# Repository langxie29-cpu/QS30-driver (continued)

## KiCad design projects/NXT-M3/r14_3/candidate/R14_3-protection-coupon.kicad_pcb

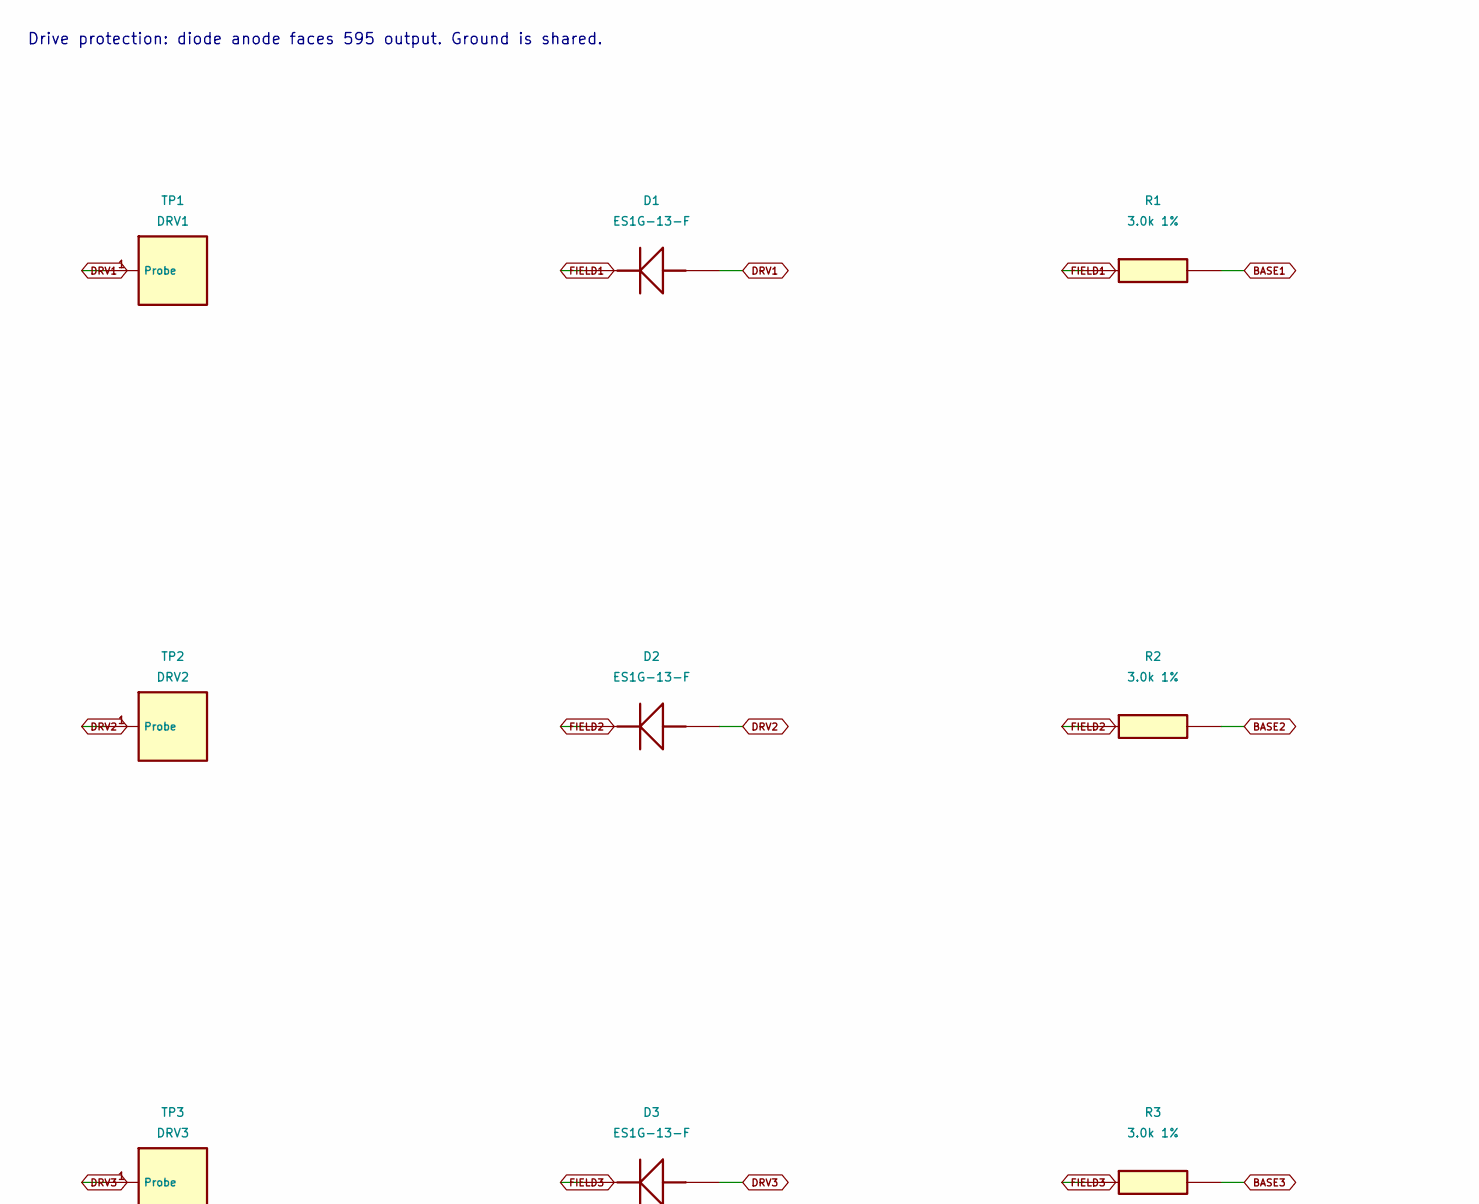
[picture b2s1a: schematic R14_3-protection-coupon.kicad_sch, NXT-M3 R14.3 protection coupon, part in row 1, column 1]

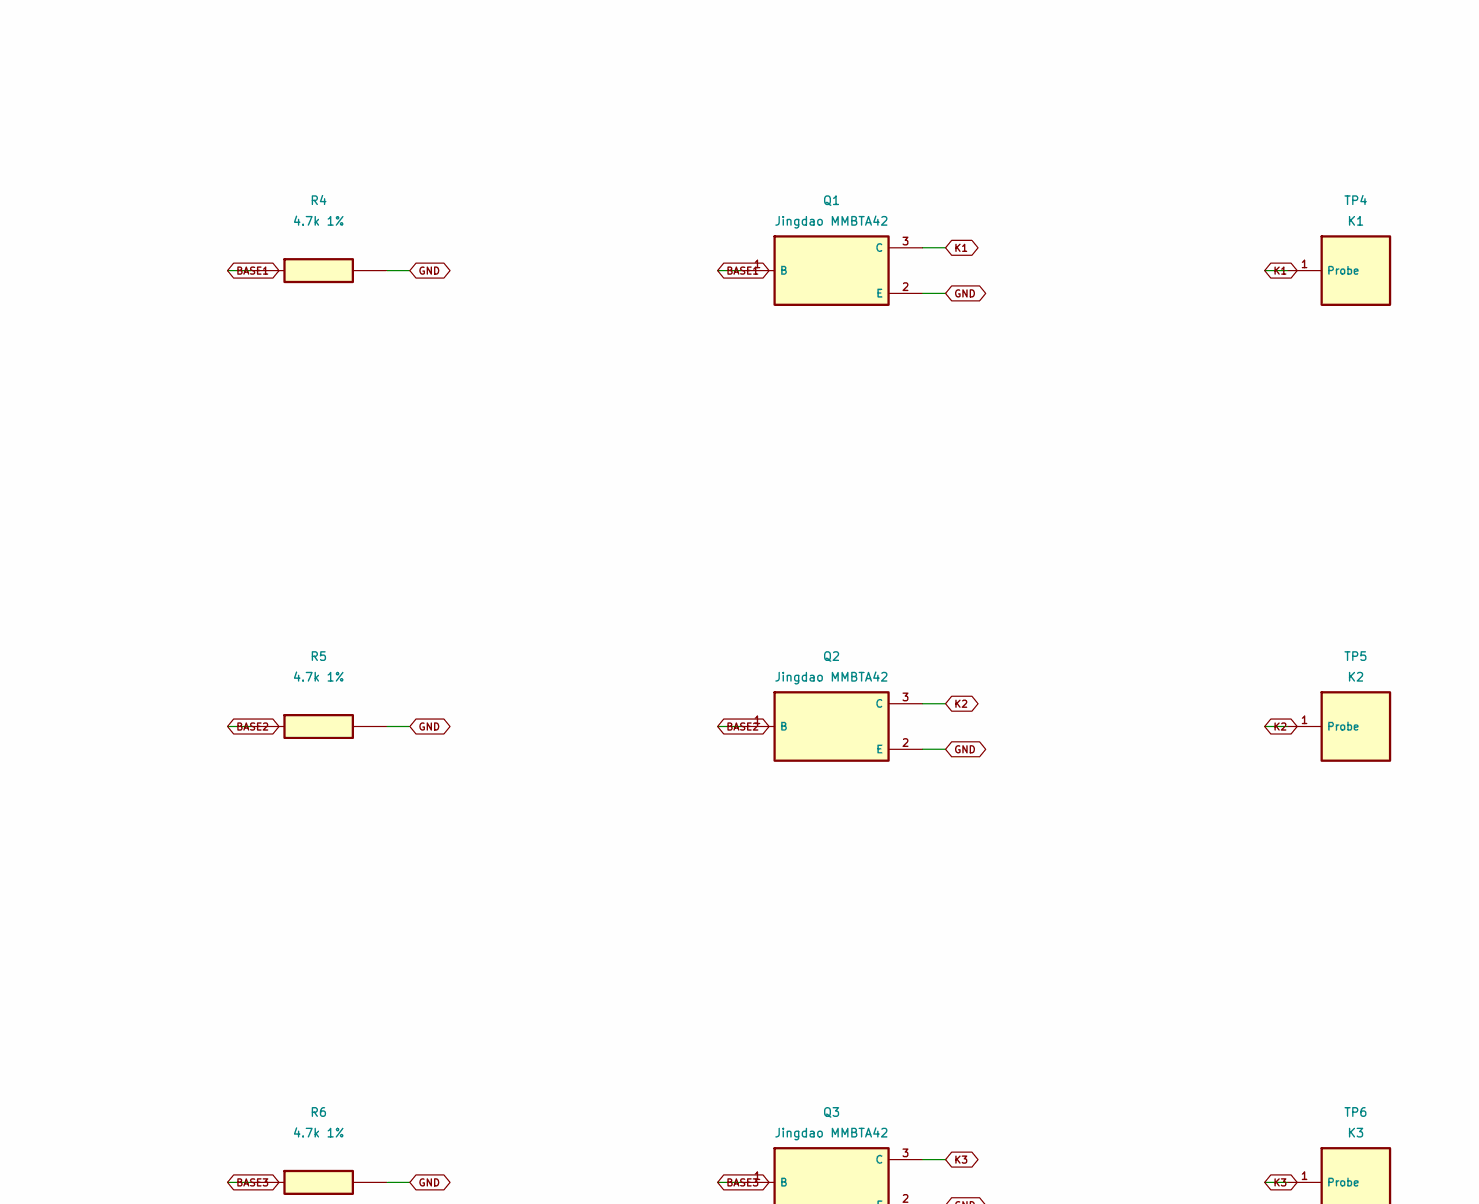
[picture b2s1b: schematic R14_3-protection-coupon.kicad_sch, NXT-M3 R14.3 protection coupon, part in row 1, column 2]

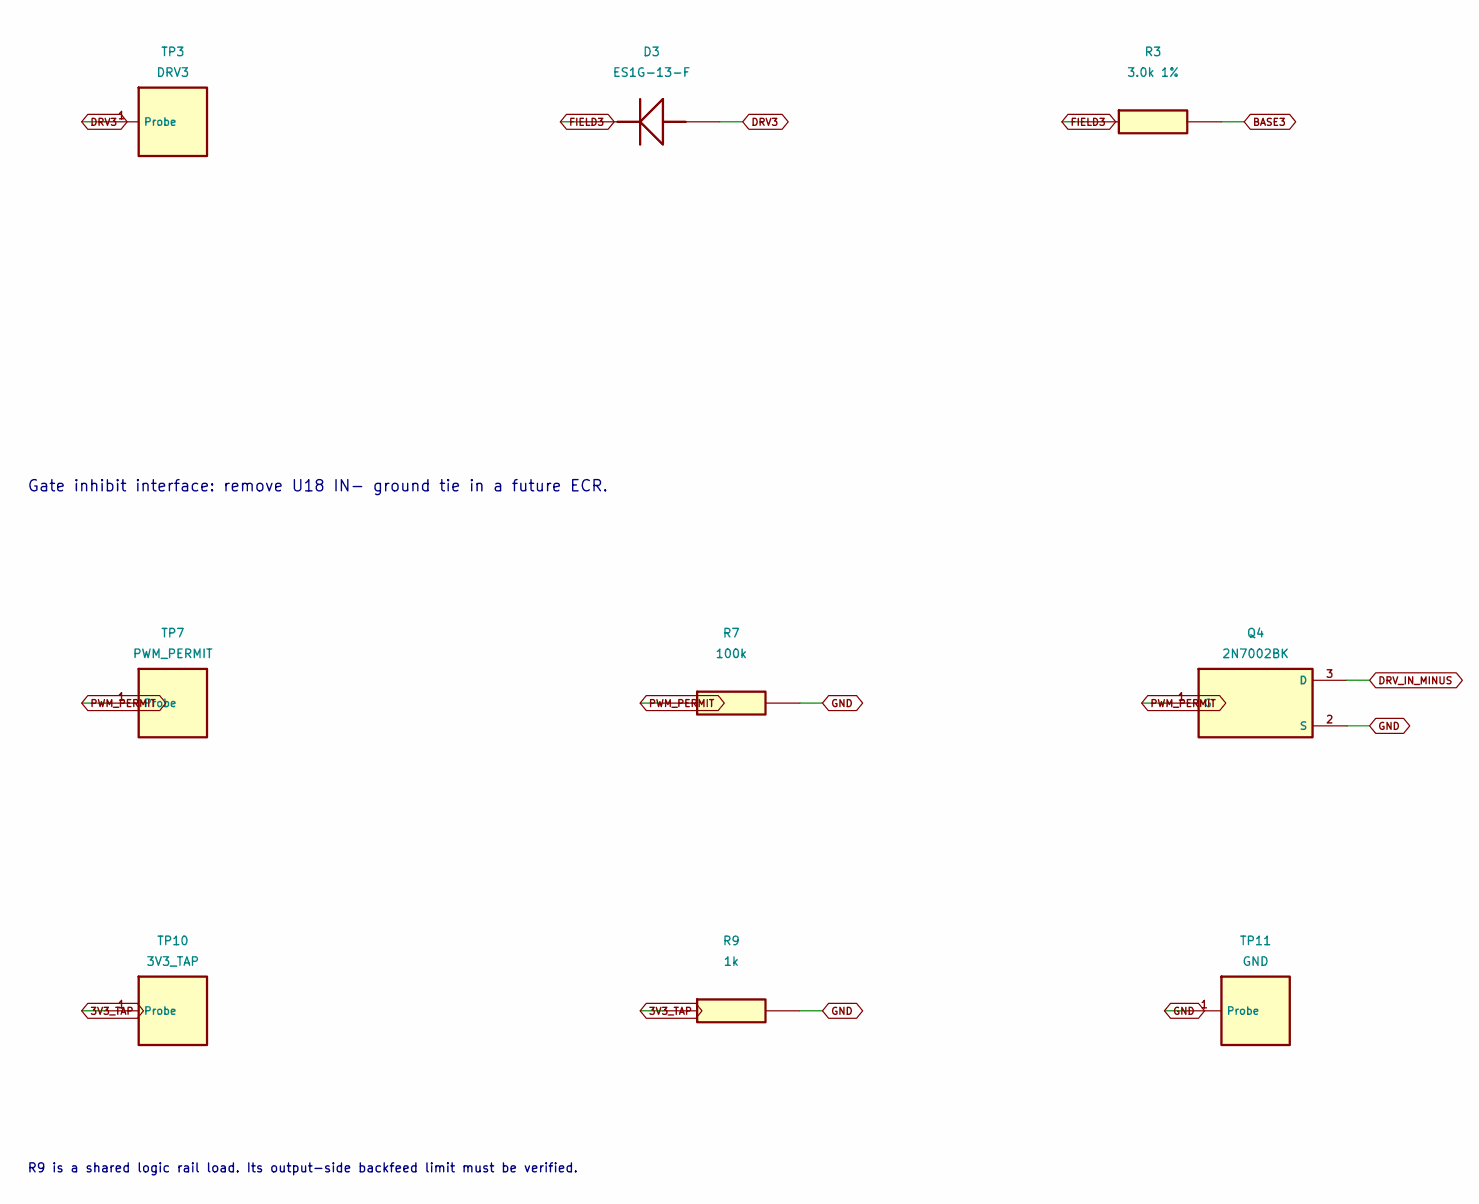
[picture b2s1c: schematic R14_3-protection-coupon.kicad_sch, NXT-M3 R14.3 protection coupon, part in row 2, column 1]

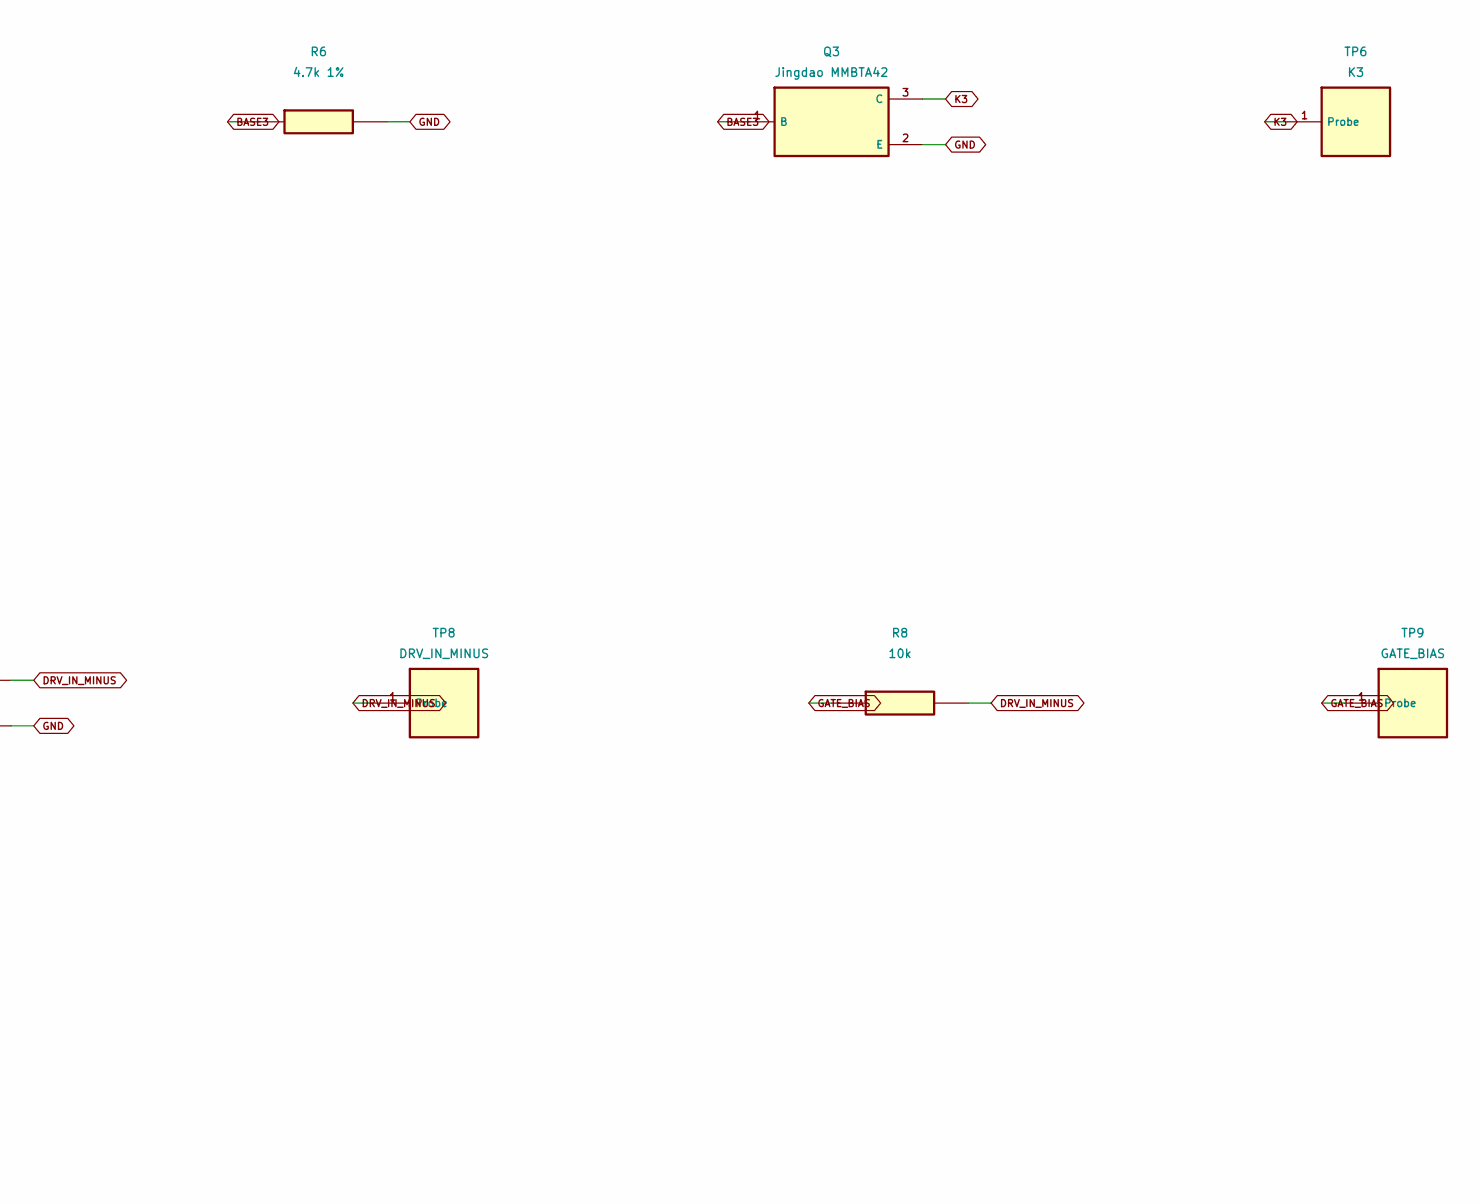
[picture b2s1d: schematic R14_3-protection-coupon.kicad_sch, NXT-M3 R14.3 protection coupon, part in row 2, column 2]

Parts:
D1, D2, D3: ES1G-13-F; D_SMA
Q1, Q2, Q3: Jingdao MMBTA42; Jingdao_MMBTA42_nominal
Q4: 2N7002BK; SOT-23
R1, R2, R3: 3.0k 1%; R_0805_2012Metric
R4, R5, R6: 4.7k 1%; R_0805_2012Metric
R7: 100k; R_0805_2012Metric
R8: 10k; R_0805_2012Metric
R9: 1k; R_0805_2012Metric
TP1: DRV1; TestPoint_Pad_D1.5mm
TP2: DRV2; TestPoint_Pad_D1.5mm
TP3: DRV3; TestPoint_Pad_D1.5mm
TP4: K1; TestPoint_Pad_D1.5mm
TP5: K2; TestPoint_Pad_D1.5mm
TP6: K3; TestPoint_Pad_D1.5mm
TP7: PWM_PERMIT; TestPoint_Pad_D1.5mm
TP8: DRV_IN_MINUS; TestPoint_Pad_D1.5mm
TP9: GATE_BIAS; TestPoint_Pad_D1.5mm
TP10: 3V3_TAP; TestPoint_Pad_D1.5mm
TP11: GND; TestPoint_Pad_D1.5mm

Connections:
3V3_TAP: R9.1, TP10.1
BASE1: Q1.1 (B), R1.2, R4.1
BASE2: Q2.1 (B), R2.2, R5.1
BASE3: Q3.1 (B), R3.2, R6.1
DRV1: D1.2 (A), TP1.1
DRV2: D2.2 (A), TP2.1
DRV3: D3.2 (A), TP3.1
DRV_IN_MINUS: Q4.3 (D), R8.2, TP8.1
FIELD1: D1.1 (K), R1.1
FIELD2: D2.1 (K), R2.1
FIELD3: D3.1 (K), R3.1
GATE_BIAS: R8.1, TP9.1
GND: Q1.2 (E), Q2.2 (E), Q3.2 (E), Q4.2 (S), R4.2, R5.2, R6.2, R7.2, R9.2, TP11.1
K1: Q1.3 (C), TP4.1
K2: Q2.3 (C), TP5.1
K3: Q3.3 (C), TP6.1
PWM_PERMIT: Q4.1 (G), R7.1, TP7.1

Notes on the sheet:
Drive protection: diode anode faces 595 output. Ground is shared.
Gate inhibit interface: remove U18 IN- ground tie in a future ECR.
R9 is a shared logic rail load. Its output-side backfeed limit must be verified.

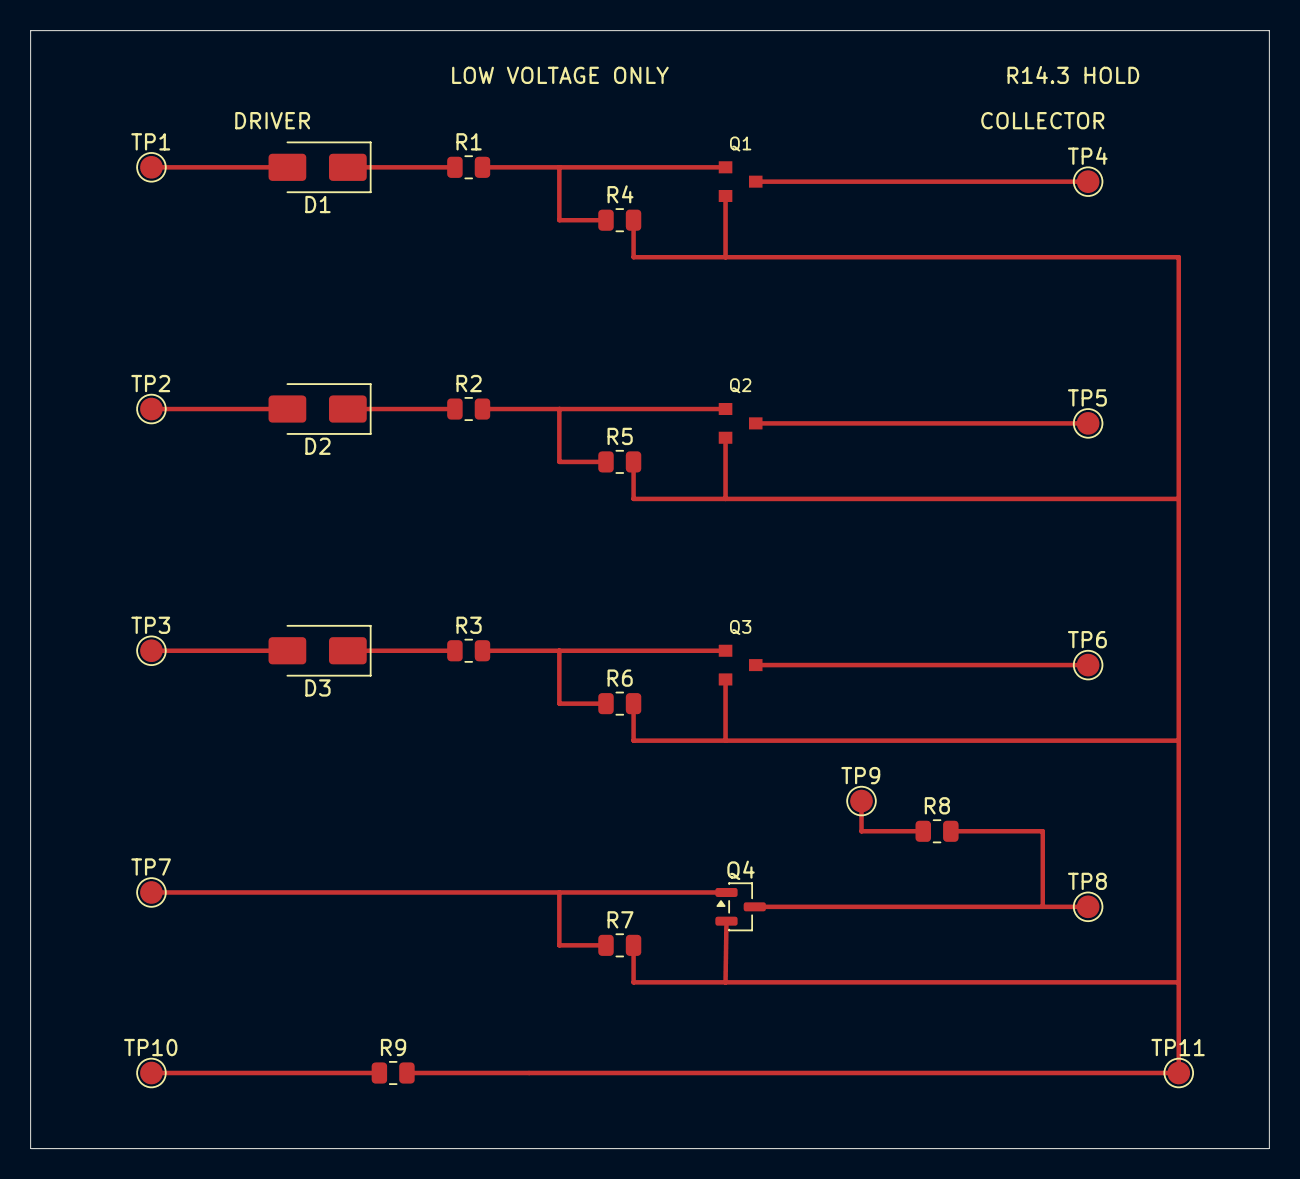
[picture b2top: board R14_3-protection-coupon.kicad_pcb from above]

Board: 2 copper layers, 82.0 x 74.0 mm, 27 parts (0 on the bottom side), 17 nets.

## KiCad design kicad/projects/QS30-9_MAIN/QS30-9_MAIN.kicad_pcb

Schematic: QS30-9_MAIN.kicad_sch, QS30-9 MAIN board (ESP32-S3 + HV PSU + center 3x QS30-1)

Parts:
C1: 10uF/25V; PRELIM_2P
C2: HV 缓冲; PRELIM_2P
C3, C4: 10 µF 250 V; PRELIM_2P
C5: CS 滤波; PRELIM_2P
C6: COMP 补偿 C; PRELIM_2P
C7: COMP 软启动; PRELIM_2P
C8: OVP 滤波; PRELIM_2P
C9: 采样滤波; PRELIM_2P
C10: 100nF/25V; PRELIM_2P
C11: BOOT 电容; PRELIM_2P
C12: 22 µF 16 V; PRELIM_2P
C13: 22 µF 10 V; PRELIM_2P
C14: EN RC; PRELIM_2P
C15: 基准滤波; PRELIM_2P
C16: CT; PRELIM_2P
C17: DOUT down-shifter decoupling; PRELIM_2P
C18: 3V3 去耦; PRELIM_2P
C19: HV 去耦; PRELIM_2P
C20: DRV_VDD 去耦; PRELIM_2P
D1: 40 V 5 A 肖特基; PRELIM_2P
D2, D4: 40 V 1 A; PRELIM_2P
D3: 1000 V 1 A 快恢复; PRELIM_2P
D5: 钳位 3V3; PRELIM_3P
F1: 1.5 A 自恢复保险丝; PRELIM_2P
J1: 12 V DC 输入; PRELIM_2P
J2: USB-C; PRELIM_20P
J3: I2C/扩展排针; PRELIM_6P
J4: UART0 恢复排针; PRELIM_6P
J5: left HV 插座; PRELIM_2P
J6: left 低压插座; PRELIM_16P
J7: right HV 插座; PRELIM_2P
J8: right 低压插座; PRELIM_16P
J9: 第 4 位管座（TBD）; PRELIM_13P
J10: 第 5 位管座（TBD）; PRELIM_13P
J11: 第 6 位管座（TBD）; PRELIM_13P
L1: 2.2 µH 2 A; PRELIM_2P
L2: 220 µH ≥5 A; PRELIM_2P
L3: 10 µH 2 A; PRELIM_2P
LED1: 状态灯; PRELIM_2P
Q1: P-FET 30 V; PRELIM_3P
Q2: 400 V 10 A; PRELIM_3P
Q3: SCR PNP; PRELIM_3P
Q4: SCR NPN; PRELIM_3P
Q5: 拉低 COMP; PRELIM_3P
Q6: 故障输出; PRELIM_3P
Q7: OVP 复位; PRELIM_3P
Q8: 拉低栅极; PRELIM_3P
Q9: HV_IN 高侧开关（30 V）; PRELIM_3P
Q10: HV_EN 驱动; PRELIM_3P
R1, R59: 5.1 kΩ CC 下拉; PRELIM_2P
R2: EN 上拉; PRELIM_2P
R3: BOOT 上拉; PRELIM_2P
R4: 栅极上拉（默认关）; PRELIM_2P
R5: Q3 基极串阻; PRELIM_2P
R6: TL431 偏置; PRELIM_2P
R7: 1.0 V 基准上（1%）; PRELIM_2P
R8: 1.0 V 基准下（1%）; PRELIM_2P
R9: DRV_SNS 上（1%）; PRELIM_2P
R10: DRV_SNS 下（1%）; PRELIM_2P
R11: 迟滞反馈; PRELIM_2P
R12: DRV_PG 上拉; PRELIM_2P
R13: FAULT_OK 上拉; PRELIM_2P
R14: EXT12_SNS 上（→10.5 V 触发）; PRELIM_2P
R15: EXT12_SNS 下; PRELIM_2P
R16: P3V3_SNS 上; PRELIM_2P
R17: P3V3_SNS 下; PRELIM_2P
R18: EXT12_PG 上拉; PRELIM_2P
R19: P3V3_PG 上拉; PRELIM_2P
R20: VREF 偏置; PRELIM_2P
R21: RT; PRELIM_2P
R22: HV 泄放 200 kΩ; PRELIM_2P
R23: FB 上（2×750k 1%）; PRELIM_2P
R24: FB 下（1%）; PRELIM_2P
R25: CS 滤波; PRELIM_2P
R26: COMP 补偿 R; PRELIM_2P
R27: HV_EN_G 上拉（默认关）; PRELIM_2P
R28: Q5 基极串阻; PRELIM_2P
R29: OVP 基准偏置; PRELIM_2P
R30: OVP 分压上（2×750k 1%）; PRELIM_2P
R31: OVP 分压下（1%）; PRELIM_2P
R32: OVP_SET 上拉; PRELIM_2P
R33: LATCH_B 上拉（保持关断）; PRELIM_2P
R34: OVP_SET→置位注入; PRELIM_2P
R35: OVP_LATCH 下拉; PRELIM_2P
R36: GPIO46 strap 下拉; PRELIM_2P
R37: Q23 基极; PRELIM_2P
R38: Q24 基极; PRELIM_2P
R39: 故障上拉; PRELIM_2P
R40, R57: 100 kΩ 1%; PRELIM_2P
R41: 故障分压上; PRELIM_2P
R42: 故障分压下（正常 1.23 V）; PRELIM_2P
R43: 复位串阻; PRELIM_2P
R44: 复位下拉; PRELIM_2P
R45: HV 采样上（2×750k）; PRELIM_2P
R46: HV 采样下; PRELIM_2P
R47: 采样串阻; PRELIM_2P
R48: 安全回路上拉; PRELIM_2P
R49: 安全回路下拉; PRELIM_2P
R50, R52, R81: 中心模块安全回路直通; PRELIM_2P
R51: 13.3 kΩ 1%; PRELIM_2P
R53: R 模块 DOUT 下拉（备用回线）; PRELIM_2P
R54: 数据链回线：L DOUT → C DIN; PRELIM_2P
R55: 数据链回线：C DOUT → R DIN; PRELIM_2P
R56: 安全回路：主板起点 → L 模块; PRELIM_2P
R58: 22.1 kΩ 1%; PRELIM_2P
R60, R62, R64: 阳极 1/2; PRELIM_2P
R61, R63, R65: 阳极 2/2; PRELIM_2P
R66, R79, R80: A9.2 default-off pull-down; PRELIM_2P
R67: HV return star bond; PRELIM_2P
R68, R69, R70, R71, R72: 3V3 domain default low; PRELIM_2P
R73: LED 限流; PRELIM_2P
R74, R75, R76, R77: 12 V 域下拉; PRELIM_2P
R78: 模块本地泄放; PRELIM_2P
SW1: BOOT 按键; PRELIM_2P
SW2, SW3, SW4: 面板按键; PRELIM_2P
TP1: HV_BUS 测试点（危险）; PRELIM_1P
U1: 5 V→3.3 V 2 A; PRELIM_5P
U2: ESP32-S3; PRELIM_41P
U3: EXT12_PG/P3V3_PG（1.0 V 基准）; PRELIM_8P
U4: USB ESD 保护; PRELIM_6P
U5: 电流型 PWM; PRELIM_8P
U6: isolated auxiliary 2.5 V ref; PRELIM_3P
U7: OVP 比较器（EXT12 供电）; PRELIM_8P
U8: OVP 2.5 V 基准; PRELIM_3P
U9: 12 V→5.08 V 2 A; PRELIM_6P
U10: 2.5 V 基准; PRELIM_3P
U11: 门控 1：DRV_VDD_EN/HV_EN; PRELIM_14P
U12: DRV_PG + FAULT_OK（3.3 V 供电/1; PRELIM_8P
U13: 门控 2：HV_EN 终级; PRELIM_14P
U14: 32 路高压驱动（PQFP-44）; PRELIM_44P
U15: 12→3.3 V DOUT; PRELIM_16P
U16: 3.3→12 V 电平转换; PRELIM_16P

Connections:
3V3: C13.1, C17.1, C18.1, D5.2 (K2), J3.1, J4.2, J6.1, J8.1, L1.2, R2.1, R3.1, R12.2, R13.2, R16.1, R18.2, R19.2, R48.1, R57.1, R73.1, U2.2 (3V3), U3.8 (VCC), U11.14 (VCC), U12.8 (VCC), U13.14 (VCC), U15.16 (VDD), U16.1 (VCC), U16.2 (ENABLE A), U16.7 (ENABLE B), U16.9 (ENABLE C), U16.15 (ENABLE D)
3V3_FB: R57.2, R58.1, U1.5 (FB)
3V3_SW: L1.1, U1.3 (LX)
5V_SYS: D2.K, D4.K, U1.1 (EN), U1.4 (IN)
A_T4: J9.2 (A), R61.2
A_T4_MID: R60.2, R61.1
A_T5: J10.2 (A), R63.2
A_T5_MID: R62.2, R63.1
A_T6: J11.2 (A), R65.2
A_T6_MID: R64.2, R65.1
BOOT_N: R3.2, SW1.1, U2.27 (IO0)
COMP_N: C7.1, Q5.3 (C), R26.1, U5.1 (COMP)
COMP_R: C6.1, R26.2
CS_FILT: C5.1, R25.2, U5.3 (CS)
DISP_ALLOW: J6.9, J8.9, R68.1, U2.8 (IO15), U16.14 (D)
DISP_CLK: J6.7, J8.7, R69.1, U2.20 (IO12), U16.6 (B)
DISP_LAT: J6.8, J8.8, R72.1, U2.22 (IO14), U16.10 (C)
DRV_PG: R11.2, R12.1, U11.9 (3A), U12.1 (OUT1)
DRV_SNS: R9.2, R10.1, R11.1, U12.3 (IN1+)
DRV_VDD: C20.1, J6.3, J8.3, Q1.3 (D), R9.1, U14.27 (POL), U14.30 (VDD), U15.1 (VCC), U15.2 (ENABLE A), U16.16 (VDD)
DRV_VDD_EN: R5.1, U11.6 (2Y)
DRV_VDD_EN_A: U11.3 (1Y), U11.4 (2A)
DRV_VDD_G: Q1.1 (G), Q8.3 (C), R4.1
EN_MCU: C14.1, R2.2, U2.3 (EN)
EXT5: C12.1, D2.A, L3.2, R40.1
EXT5_BOOT: C11.1, U9.6 (BOOT)
EXT5_FB: R40.2, R51.1, U9.4 (FB)
EXT5_SW: C11.2, L3.1, U9.2 (SW)
EXT12: C1.1, C10.1, D1.K, Q1.2 (S), Q3.2 (E), Q9.2 (S), R4.2, R6.1, R14.1, R20.1, R27.2, R29.1, R32.2, R33.2, R39.2, U7.8 (VCC), U9.3 (VIN), U9.5 (EN)
EXT12_F: D1.A, F1.2
EXT12_PG: R18.1, U3.1 (OUT1), U11.1 (1A)
EXT12_RAW: F1.1, J1.1
EXT12_SNS: R14.2, R15.1, U3.3 (IN1+)
FAULT_OK: R13.1, U11.10 (3B), U12.7 (OUT2)
FB_HV: R23.2, R24.1, U5.2 (FB)
GND: C1.2, C5.2, C6.2, C7.2, C8.2, C9.2, C10.2, C12.2, C13.2, C14.2, C15.2, C16.2, C17.2, C18.2, C20.2, D5.1 (A1), J1.2, J2.A1 (GND), J2.A12 (GND), J2.B1 (GND), J2.B12 (GND), J2.S1 (SHIELD), J2.S2 (SHIELD), J2.S3 (SHIELD), J2.S4 (SHIELD), J3.2, J3.5, J3.6, J4.1, J4.5, J4.6, J6.2, J6.4, J6.12, J6.13, J6.14, J6.15, J6.16, J8.2, J8.4, J8.12, J8.13, J8.14, J8.15, J8.16, Q2.3 (S), Q4.2 (E), Q5.2 (E), Q6.2 (E), Q7.2 (E), Q8.2 (E), Q10.2 (E), R1.2, R8.2, R10.2, R15.2, R17.2, R24.2, R31.2, R35.2, R36.2, R42.2, R44.2, R46.2, R49.2, R51.2, R53.2, R58.2, R59.2, R66.2, R67.2, R68.2, R69.2, R70.2, R71.2, R72.2, R74.2, R75.2, R76.2, R77.2, R79.2, R80.2, SW1.2, SW2.2, SW3.2, SW4.2, U1.2 (GND), U2.1 (GND), U2.40 (GND), U2.41 (GND/EP), U3.4 (GND), U4.2 (GND), U5.5 (GND), U6.3 (ANODE), U7.4 (GND), U7.5 (IN2+), U8.3 (ANODE), U9.1 (GND), U10.3 (ANODE), U11.7 (GND), U12.4 (GND), U13.4 (2A), U13.5 (2B), U13.7 (GND), U13.9 (3A), U13.10 (3B), U13.12 (4A), U13.13 (4B), U14.29 (VSS), U15.6 (B), U15.7 (ENABLE B), U15.8 (VSS), U15.9 (ENABLE C), U15.10 (C), U15.14 (D), U15.15 (ENABLE D), U16.8 (VSS)
GND_HV: C3.2, C4.2, C19.2, J5.2 (HV_RET), J7.2 (HV_RET), R22.2, R67.1, R78.2
GPIO46_STRAP: R36.1, U2.16 (IO46)
HVF_NODE: D5.3 (C), R41.2, R42.1, U2.7 (IO7), U12.5 (IN2+)
HV_BUS: C2.2, C3.1, C4.1, C19.1, D3.K, J5.1 (HV+), J7.1 (HV+), R22.1, R23.1, R30.1, R45.1, R60.1, R62.1, R64.1, R78.1, TP1.1
HV_EN: R28.1, U13.3 (1Y)
HV_EN_A: U11.8 (3Y), U11.12 (4A)
HV_EN_B: U11.11 (4Y), U13.1 (1A)
HV_EN_G: Q9.1 (G), Q10.3 (C), R27.1
HV_EN_REQ: R66.1, U2.9 (IO16), U11.5 (2B), U13.2 (1B)
HV_FAULT_OD: Q6.3 (C), R39.1, R41.1
HV_GATE: Q2.1 (G), U5.6 (OUT)
HV_IN: L2.1, Q9.3 (D), U5.7 (VCC)
HV_SENSE_ADC: C9.1, R47.2, U2.39 (IO1)
HV_SENSE_MID: R45.2, R46.1, R47.1
I2C_SCL: J3.3, U2.17 (IO9)
I2C_SDA: J3.4, U2.12 (IO8)
KEY_MINUS: SW4.1, U2.6 (IO6)
KEY_PLUS: SW3.1, U2.5 (IO5)
KEY_SET: SW2.1, U2.4 (IO4)
K_T4_0: J9.3 (K0), U14.22 (HVOUT1)
K_T4_1: J9.13 (K1), U14.21 (HVOUT2)
K_T4_2: J9.12 (K2), U14.20 (HVOUT3)
K_T4_3: J9.11 (K3), U14.19 (HVOUT4)
K_T4_4: J9.10 (K4), U14.18 (HVOUT5)
K_T4_5: J9.9 (K5), U14.17 (HVOUT6)
K_T4_6: J9.7 (K6), U14.16 (HVOUT7)
K_T4_7: J9.6 (K7), U14.15 (HVOUT8)
K_T4_8: J9.5 (K8), U14.14 (HVOUT9)
K_T4_9: J9.4 (K9), U14.13 (HVOUT10)
K_T5_0: J10.3 (K0), U14.12 (HVOUT11)
K_T5_1: J10.13 (K1), U14.11 (HVOUT12)
K_T5_2: J10.12 (K2), U14.10 (HVOUT13)
K_T5_3: J10.11 (K3), U14.9 (HVOUT14)
K_T5_4: J10.10 (K4), U14.8 (HVOUT15)
K_T5_5: J10.9 (K5), U14.7 (HVOUT16)
K_T5_6: J10.7 (K6), U14.6 (HVOUT17)
K_T5_7: J10.6 (K7), U14.5 (HVOUT18)
K_T5_8: J10.5 (K8), U14.4 (HVOUT19)
K_T5_9: J10.4 (K9), U14.3 (HVOUT20)
K_T6_0: J11.3 (K0), U14.2 (HVOUT21)
K_T6_1: J11.13 (K1), U14.1 (HVOUT22)
K_T6_2: J11.12 (K2), U14.44 (HVOUT23)
K_T6_3: J11.11 (K3), U14.43 (HVOUT24)
K_T6_4: J11.10 (K4), U14.42 (HVOUT25)
K_T6_5: J11.9 (K5), U14.41 (HVOUT26)
K_T6_6: J11.7 (K6), U14.40 (HVOUT27)
K_T6_7: J11.6 (K7), U14.39 (HVOUT28)
K_T6_8: J11.5 (K8), U14.38 (HVOUT29)
K_T6_9: J11.4 (K9), U14.37 (HVOUT30)
LATCH_B: Q3.1 (B), Q4.3 (C), R33.1, R34.2
LED_A: LED1.1 (K), R73.2
MOD_C_DIN: R54.2, R70.1, U16.3 (A)
MOD_C_DOUT: R55.1, R71.1, U15.4 (E)
MOD_L_DIN: J6.5, U2.19 (IO11)
MOD_L_DOUT: J6.6, R54.1
MOD_R_DIN: J8.5, R55.2
MOD_R_DOUT: J8.6, R53.1
OVP_LATCH: Q3.3 (C), Q4.1 (B), Q7.3 (C), R35.1, R37.1, R38.1
OVP_RST: R43.1, U2.11 (IO18)
OVP_RST_G: Q7.1 (B), R43.2, R44.1
OVP_SET: R32.1, R34.1, U7.1 (OUT1)
OVP_SNS: C8.1, R30.2, R31.1, U7.2 (IN1-)
P3V3_PG: R19.1, U3.7 (OUT2), U11.2 (1B)
P3V3_SNS: R16.2, R17.1, U3.5 (IN2+)
Q3_B: Q8.1 (B), R5.2, R79.1
Q5_B: Q10.1 (B), R28.2, R80.1
Q23_B: Q5.1 (B), R37.2
Q24_B: Q6.1 (B), R38.2
RT_CT: C16.1, R21.1, U5.4 (RT/CT)
SAFETY_LOOP_C_IN: R50.2, R81.1
SAFETY_LOOP_C_OUT: R52.1, R81.2
SAFETY_LOOP_L_IN: J6.10, R56.2
SAFETY_LOOP_L_OUT: J6.11, R50.1
SAFETY_LOOP_MAIN: R48.2, R56.1
SAFETY_LOOP_R_IN: J8.10, R52.2
SAFETY_LOOP_R_OUT: J8.11, R49.1, U2.24 (IO47), U11.13 (4B)
STATUS_LED: LED1.2 (A), U2.10 (IO17)
SW_HV: C2.1, D3.A, L2.2, Q2.2 (D), R25.1
UART0_RX: J4.4, U2.36 (IO44/RXD0)
UART0_TX: J4.3, U2.37 (IO43/TXD0)
USB_CC1: J2.A5 (CC1), R59.1
USB_CC2: J2.B5 (CC2), R1.1
USB_DM: J2.A7 (D-), J2.B7 (D-), U4.3 (I/O2)
USB_DM_MCU: U2.13 (IO19), U4.4 (I/O2)
USB_DP: J2.A6 (D+), J2.B6 (D+), U4.1 (I/O1)
USB_DP_MCU: U2.14 (IO20), U4.6 (I/O1)
U_C_BL: R74.1, U14.33 (BL), U16.13 (H)
U_C_CLK: R75.1, U14.28 (CLK), U16.5 (F)
U_C_DIN: R76.1, U14.32 (DATA IN), U16.4 (E)
U_C_DOUT: U14.23 (DATA OUT), U15.3 (A)
U_C_LAT: R77.1, U14.31 (LE), U16.11 (G)
VBUS: D4.A, J2.A4 (VBUS), J2.A9 (VBUS), J2.B4 (VBUS), J2.B9 (VBUS), U4.5 (VBUS)
VREF_1V0: C15.1, R7.2, R8.1, U3.2 (IN1-), U3.6 (IN2-), U12.2 (IN1-), U12.6 (IN2-)
VREF_2V5: R6.2, R7.1, U10.1 (CATHODE), U10.2 (REF)
VREF_AUX_2V5: R20.2, U6.1 (CATHODE), U6.2 (REF)
VREF_OVP: R29.2, U7.3 (IN1+), U7.6 (IN2-), U8.1 (CATHODE), U8.2 (REF)
VREF_UC: R21.2, U5.8 (VREF)

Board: 2 copper layers, 157 parts (0 on the bottom side), 133 nets, no tracks yet.

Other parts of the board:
H44, H486, H1164, H11686: MountingHole_3.2mm

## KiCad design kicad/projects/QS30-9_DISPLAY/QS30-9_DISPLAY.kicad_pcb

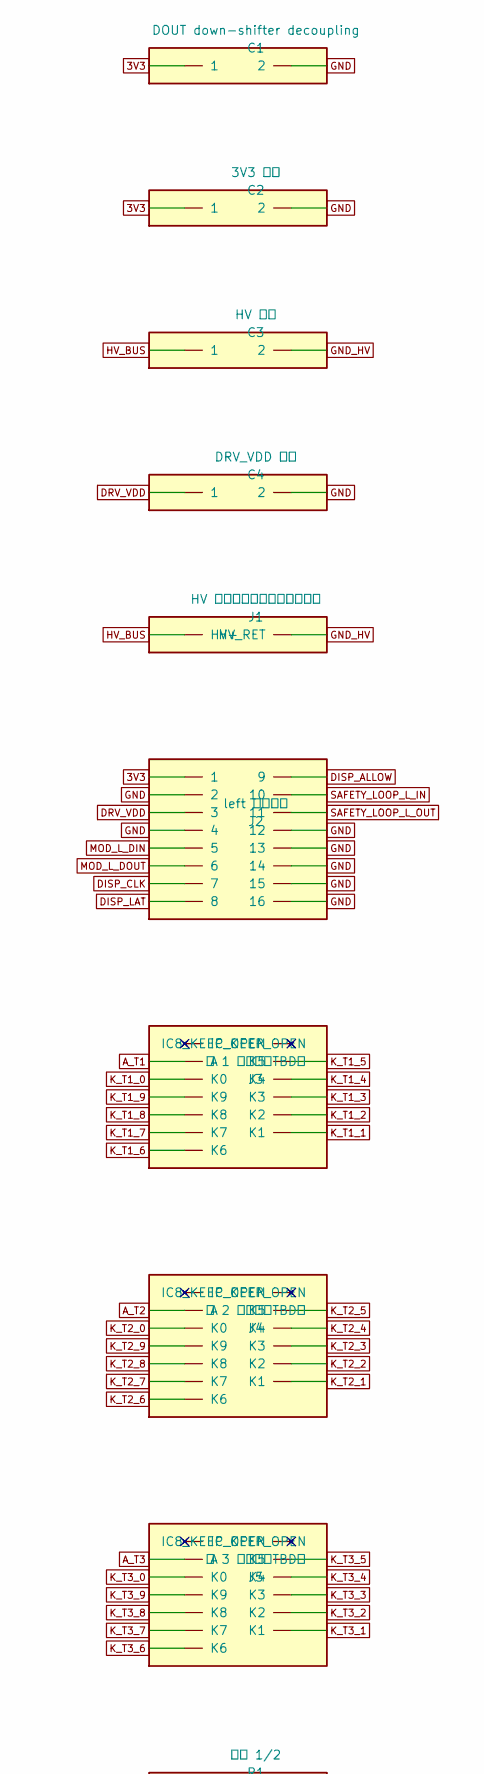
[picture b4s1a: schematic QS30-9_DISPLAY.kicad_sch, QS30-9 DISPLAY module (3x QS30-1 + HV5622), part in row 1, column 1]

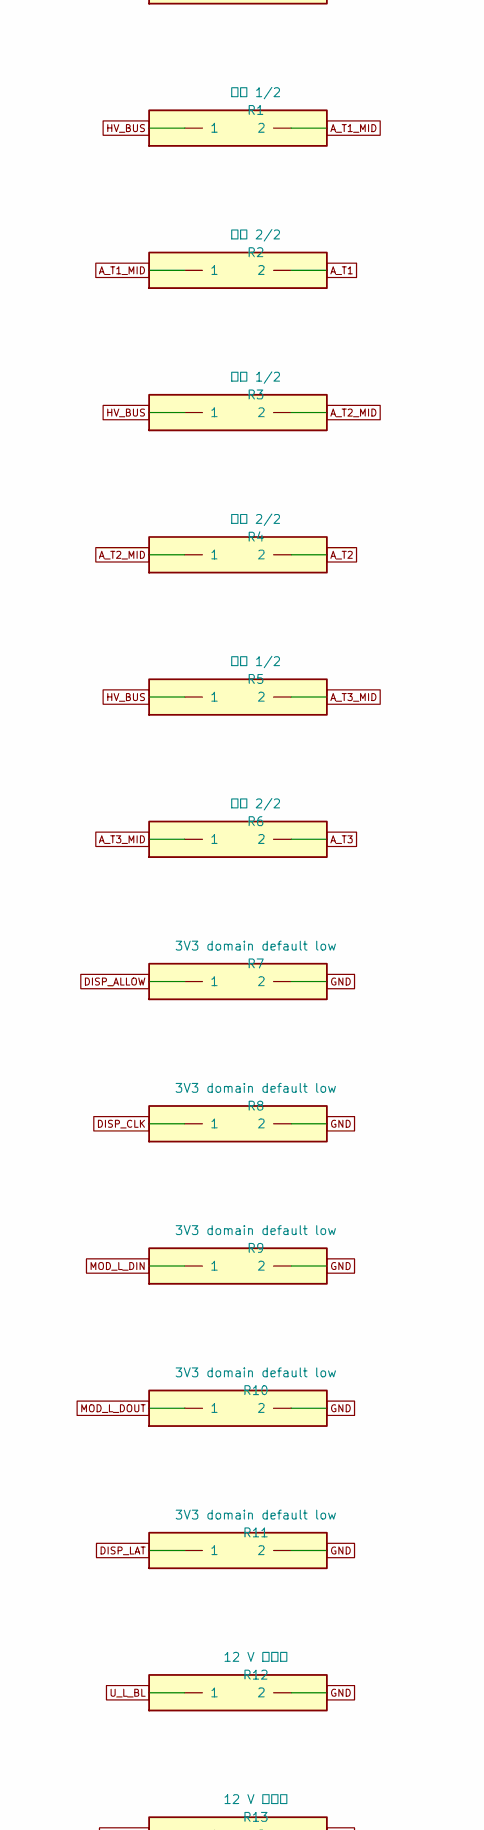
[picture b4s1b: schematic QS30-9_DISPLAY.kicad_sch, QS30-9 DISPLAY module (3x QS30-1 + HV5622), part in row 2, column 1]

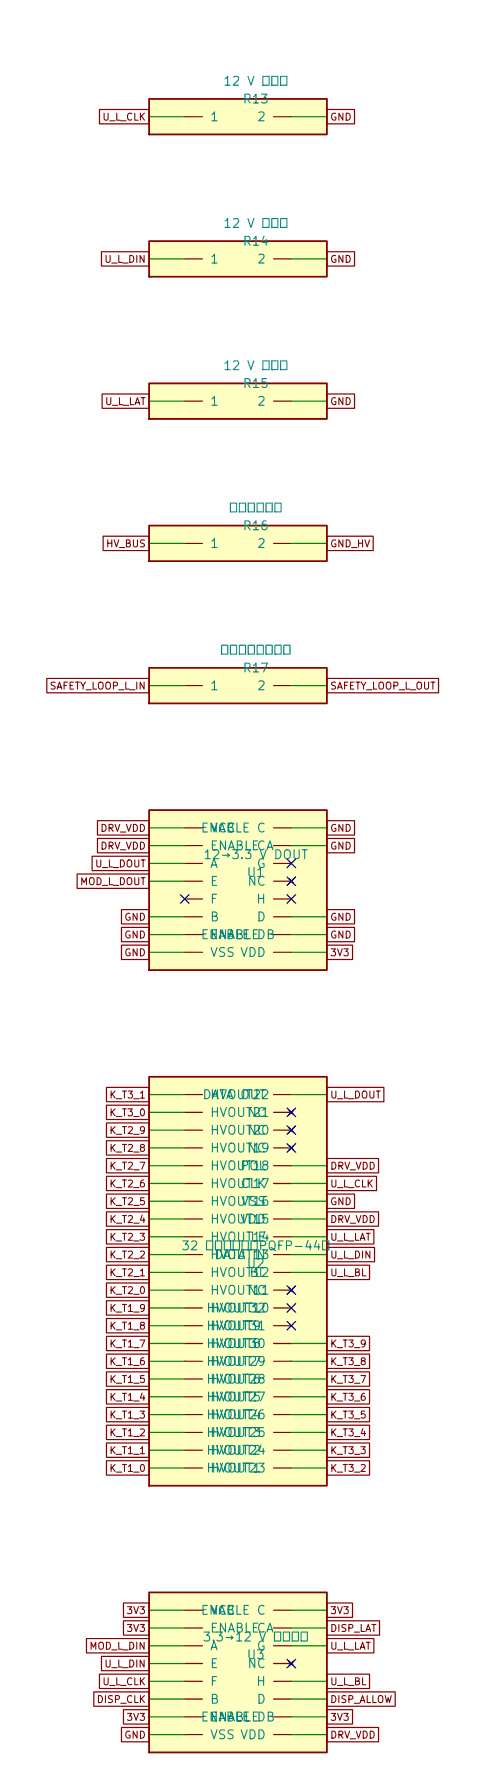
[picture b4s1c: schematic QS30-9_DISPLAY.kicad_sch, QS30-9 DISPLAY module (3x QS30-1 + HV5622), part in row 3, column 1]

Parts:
C1: DOUT down-shifter decoupling; PRELIM_2P
C2: 3V3 去耦; PRELIM_2P
C3: HV 去耦; PRELIM_2P
C4: DRV_VDD 去耦; PRELIM_2P
J1: HV 接口（防触碰，额定待核）; PRELIM_2P
J2: left 低压接口; PRELIM_16P
J3: 第 1 位管座（TBD）; PRELIM_13P
J4: 第 2 位管座（TBD）; PRELIM_13P
J5: 第 3 位管座（TBD）; PRELIM_13P
R1, R3, R5: 阳极 1/2; PRELIM_2P
R2, R4, R6: 阳极 2/2; PRELIM_2P
R7, R8, R9, R10, R11: 3V3 domain default low; PRELIM_2P
R12, R13, R14, R15: 12 V 域下拉; PRELIM_2P
R16: 模块本地泄放; PRELIM_2P
R17: 模块安全回路直通; PRELIM_2P
U1: 12→3.3 V DOUT; PRELIM_16P
U2: 32 路高压驱动（PQFP-44）; PRELIM_44P
U3: 3.3→12 V 电平转换; PRELIM_16P

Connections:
3V3: C1.1, C2.1, J2.1, U1.16 (VDD), U3.1 (VCC), U3.2 (ENABLE A), U3.7 (ENABLE B), U3.9 (ENABLE C), U3.15 (ENABLE D)
A_T1: J3.2 (A), R2.2
A_T1_MID: R1.2, R2.1
A_T2: J4.2 (A), R4.2
A_T2_MID: R3.2, R4.1
A_T3: J5.2 (A), R6.2
A_T3_MID: R5.2, R6.1
DISP_ALLOW: J2.9, R7.1, U3.14 (D)
DISP_CLK: J2.7, R8.1, U3.6 (B)
DISP_LAT: J2.8, R11.1, U3.10 (C)
DRV_VDD: C4.1, J2.3, U1.1 (VCC), U1.2 (ENABLE A), U2.27 (POL), U2.30 (VDD), U3.16 (VDD)
GND: C1.2, C2.2, C4.2, J2.2, J2.4, J2.12, J2.13, J2.14, J2.15, J2.16, R7.2, R8.2, R9.2, R10.2, R11.2, R12.2, R13.2, R14.2, R15.2, U1.6 (B), U1.7 (ENABLE B), U1.8 (VSS), U1.9 (ENABLE C), U1.10 (C), U1.14 (D), U1.15 (ENABLE D), U2.29 (VSS), U3.8 (VSS)
GND_HV: C3.2, J1.2 (HV_RET), R16.2
HV_BUS: C3.1, J1.1 (HV+), R1.1, R3.1, R5.1, R16.1
K_T1_0: J3.3 (K0), U2.22 (HVOUT1)
K_T1_1: J3.13 (K1), U2.21 (HVOUT2)
K_T1_2: J3.12 (K2), U2.20 (HVOUT3)
K_T1_3: J3.11 (K3), U2.19 (HVOUT4)
K_T1_4: J3.10 (K4), U2.18 (HVOUT5)
K_T1_5: J3.9 (K5), U2.17 (HVOUT6)
K_T1_6: J3.7 (K6), U2.16 (HVOUT7)
K_T1_7: J3.6 (K7), U2.15 (HVOUT8)
K_T1_8: J3.5 (K8), U2.14 (HVOUT9)
K_T1_9: J3.4 (K9), U2.13 (HVOUT10)
K_T2_0: J4.3 (K0), U2.12 (HVOUT11)
K_T2_1: J4.13 (K1), U2.11 (HVOUT12)
K_T2_2: J4.12 (K2), U2.10 (HVOUT13)
K_T2_3: J4.11 (K3), U2.9 (HVOUT14)
K_T2_4: J4.10 (K4), U2.8 (HVOUT15)
K_T2_5: J4.9 (K5), U2.7 (HVOUT16)
K_T2_6: J4.7 (K6), U2.6 (HVOUT17)
K_T2_7: J4.6 (K7), U2.5 (HVOUT18)
K_T2_8: J4.5 (K8), U2.4 (HVOUT19)
K_T2_9: J4.4 (K9), U2.3 (HVOUT20)
K_T3_0: J5.3 (K0), U2.2 (HVOUT21)
K_T3_1: J5.13 (K1), U2.1 (HVOUT22)
K_T3_2: J5.12 (K2), U2.44 (HVOUT23)
K_T3_3: J5.11 (K3), U2.43 (HVOUT24)
K_T3_4: J5.10 (K4), U2.42 (HVOUT25)
K_T3_5: J5.9 (K5), U2.41 (HVOUT26)
K_T3_6: J5.7 (K6), U2.40 (HVOUT27)
K_T3_7: J5.6 (K7), U2.39 (HVOUT28)
K_T3_8: J5.5 (K8), U2.38 (HVOUT29)
K_T3_9: J5.4 (K9), U2.37 (HVOUT30)
MOD_L_DIN: J2.5, R9.1, U3.3 (A)
MOD_L_DOUT: J2.6, R10.1, U1.4 (E)
SAFETY_LOOP_L_IN: J2.10, R17.1
SAFETY_LOOP_L_OUT: J2.11, R17.2
U_L_BL: R12.1, U2.33 (BL), U3.13 (H)
U_L_CLK: R13.1, U2.28 (CLK), U3.5 (F)
U_L_DIN: R14.1, U2.32 (DATA IN), U3.4 (E)
U_L_DOUT: U1.3 (A), U2.23 (DATA OUT)
U_L_LAT: R15.1, U2.31 (LE), U3.11 (G)

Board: 2 copper layers, 33 parts (0 on the bottom side), 53 nets, no tracks yet.

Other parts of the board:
H44, H496, H964, H9696: MountingHole_3.2mm
